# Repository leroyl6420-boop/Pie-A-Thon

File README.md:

# Pie-A-Thon
My first software project, coded in Python! You bake pies in a pie restaurant, so that's why it's called the Pie-A-Thon! It also sounds like "Python" when you say it fast (:

# How To Play

There are two things you need in every pie: a crust and a jam. 

Get jams by collecting fruits at the ingredient station. 

Afterwards, go to the jam station and mash the fruits into jam by turning the Jam-o-Matic's crank. There are four types of fruit and thus four types of jam: apple, blueberry, cherry, and pumpkin. 

Start your crust by collecting three scoops of flour at the flour station. Drag the spoon between the bag of flour and the bowl.

Visit the dough and crust stations, in that order. You will get a crust. After collecting one crust and at least one jam, head over to the assembly station to assemble a pie. The crust will be in the center and the jams you have collected will be at the bottom. Select the jams you would like to use, and they will be moved to the side of the pie. Press "E" when you are done choosing. You will get an unbaked pie. The same will happen if you run out of jam. 

Head over to either one of the two ovens to bake your pie. They will take at least six seconds before the progress bar turns from yellow to green. That will mean that they are ready. You will have nine seconds before the progress bar turns red and the pie burns. Each oven may only bake one pie at a time. 

Serve the pie to your customers! Each served pie will give you one point. Try not to keep your customers waiting too long!

# Future Plans

In the future, I plan to add a customer ordering system where customers my order pies of specific flavors/combinations. I may also add a mechanism where customers may get angry if they wait too long and leave. Finally, I could potentially add a day-in ordering system and money so that you'll have to predict what customers will order and not go broke. All in all, this game has tons of potential!

# First-Run-Steps

Just download the Pie-A-Thon.zip file in the repository, or open the link here! 

https://github.com/leroyl6420-boop/Pie-A-Thon/raw/refs/heads/main/Pie-A-Thon.zip

Extract the contents, enter the Main folder and run Pie-A-Thon.exe! Your computer may try to stop you on account of potential viruses. Don't worry, there aren't any!* Just ignore the warnings, and have fun!

# AI Use

AI was used only to find bugs in this project. The AI in question is VS Code's free Copilot. 

*or are there?

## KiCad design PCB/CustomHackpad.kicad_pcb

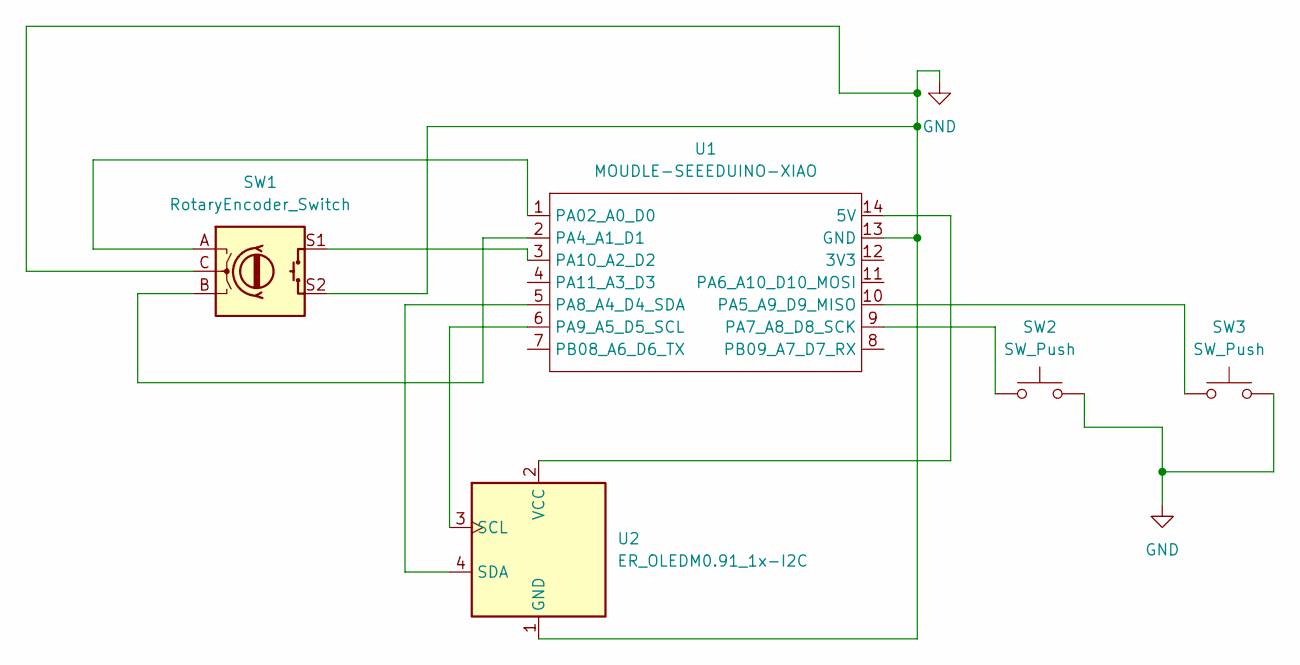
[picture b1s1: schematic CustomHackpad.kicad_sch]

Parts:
SW1: RotaryEncoder_Switch; RotaryEncoder_Alps_EC11E-Switch_Vertical_H20mm
SW2, SW3: SW_Push; SW_Cherry_MX_1.00u_PCB
U1: MOUDLE-SEEEDUINO-XIAO; XIAO-Generic-Hybrid-14P-2.54-21X17.8MM
U2: ER_OLEDM0.91_1x-I2C

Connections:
GND: SW1.C, SW1.S2, SW2.2, SW3.2, U1.13 (GND), U2.1 (GND)
unnamed: U1.14 (5V), U2.2 (VCC)
unnamed: SW1.A, U1.1 (PA02_A0_D0)
unnamed: SW1.B, U1.2 (PA4_A1_D1)
unnamed: SW3.1, U1.10 (PA5_A9_D9_MISO)
unnamed: SW2.1, U1.9 (PA7_A8_D8_SCK)
unnamed: U1.5 (PA8_A4_D4_SDA), U2.4 (SDA)
unnamed: U1.6 (PA9_A5_D5_SCL), U2.3 (SCL)
unnamed: SW1.S1, U1.3 (PA10_A2_D2)

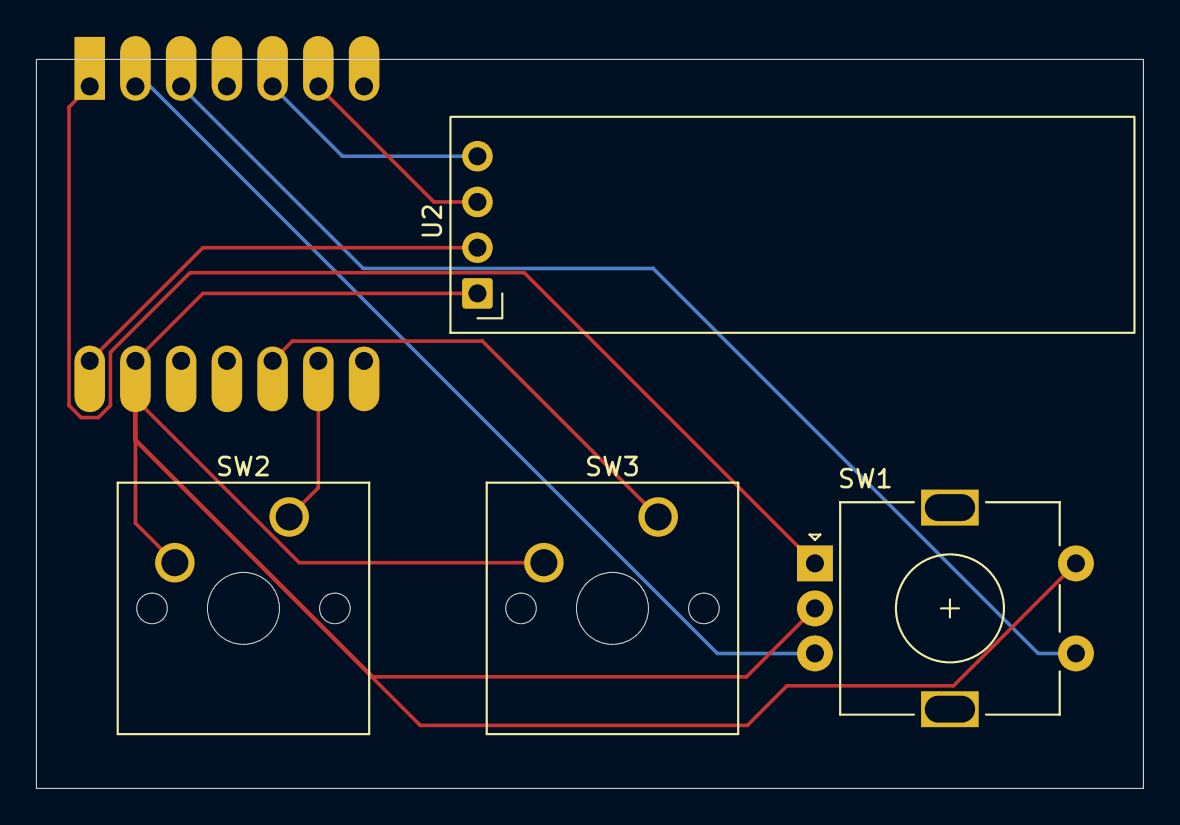
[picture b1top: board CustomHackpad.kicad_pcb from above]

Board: 2 copper layers, 61.5 x 40.5 mm, 5 parts (1 on the bottom side), 9 nets.
